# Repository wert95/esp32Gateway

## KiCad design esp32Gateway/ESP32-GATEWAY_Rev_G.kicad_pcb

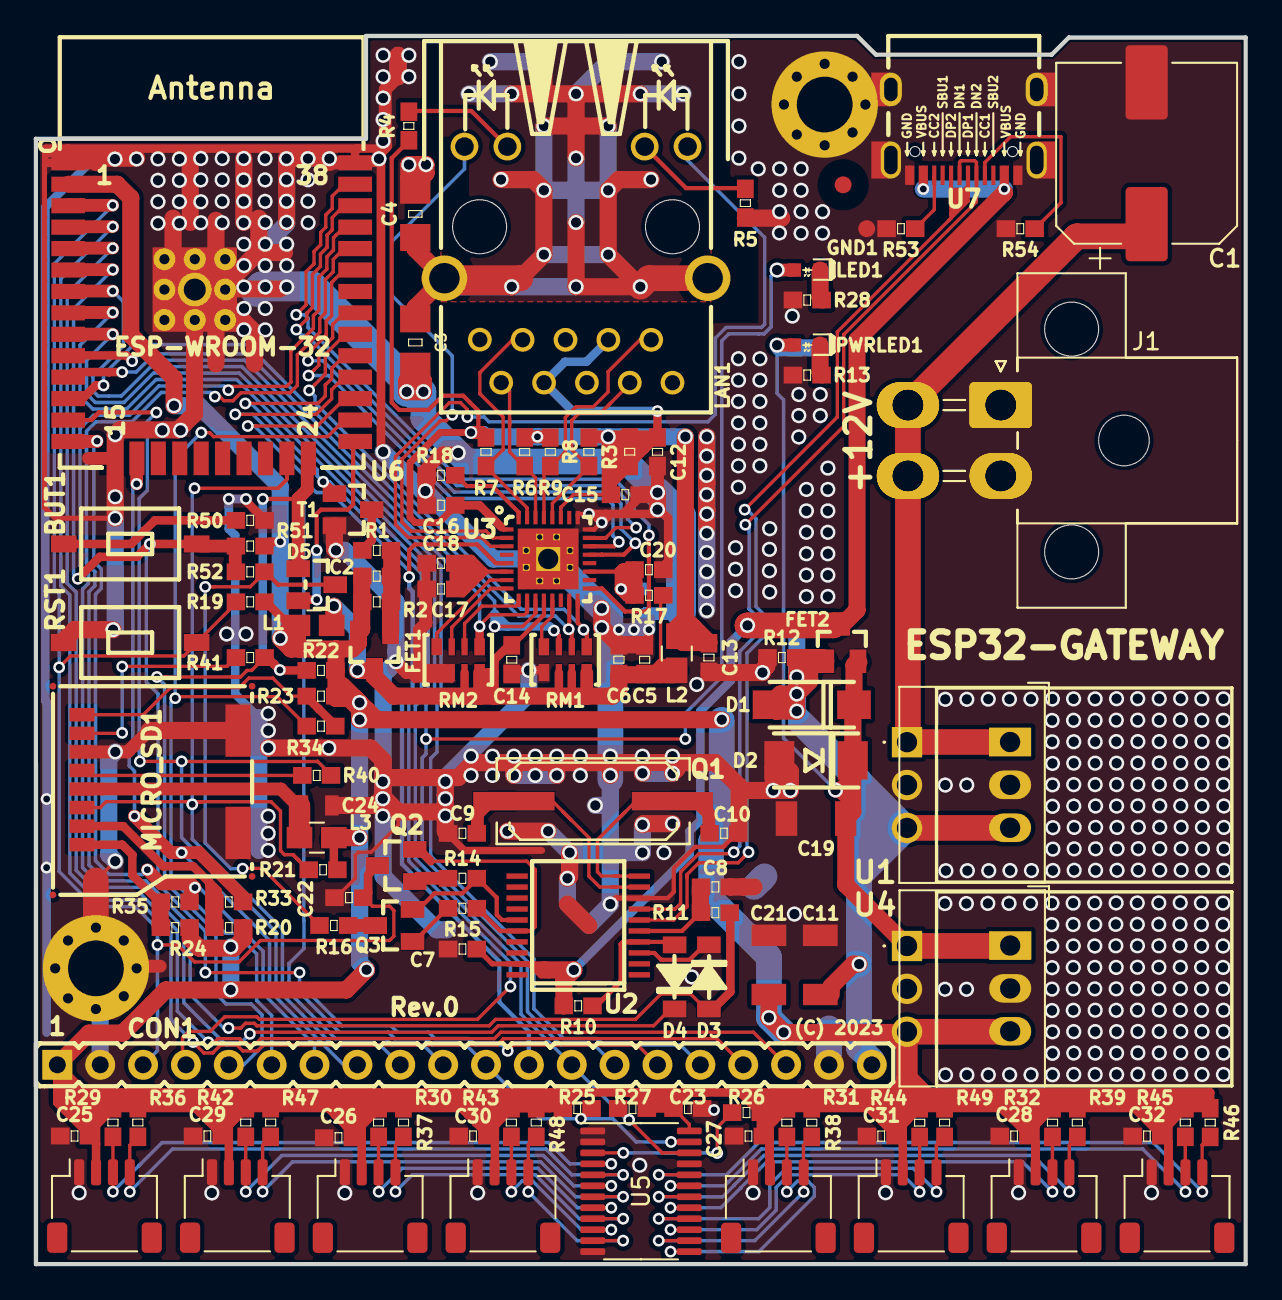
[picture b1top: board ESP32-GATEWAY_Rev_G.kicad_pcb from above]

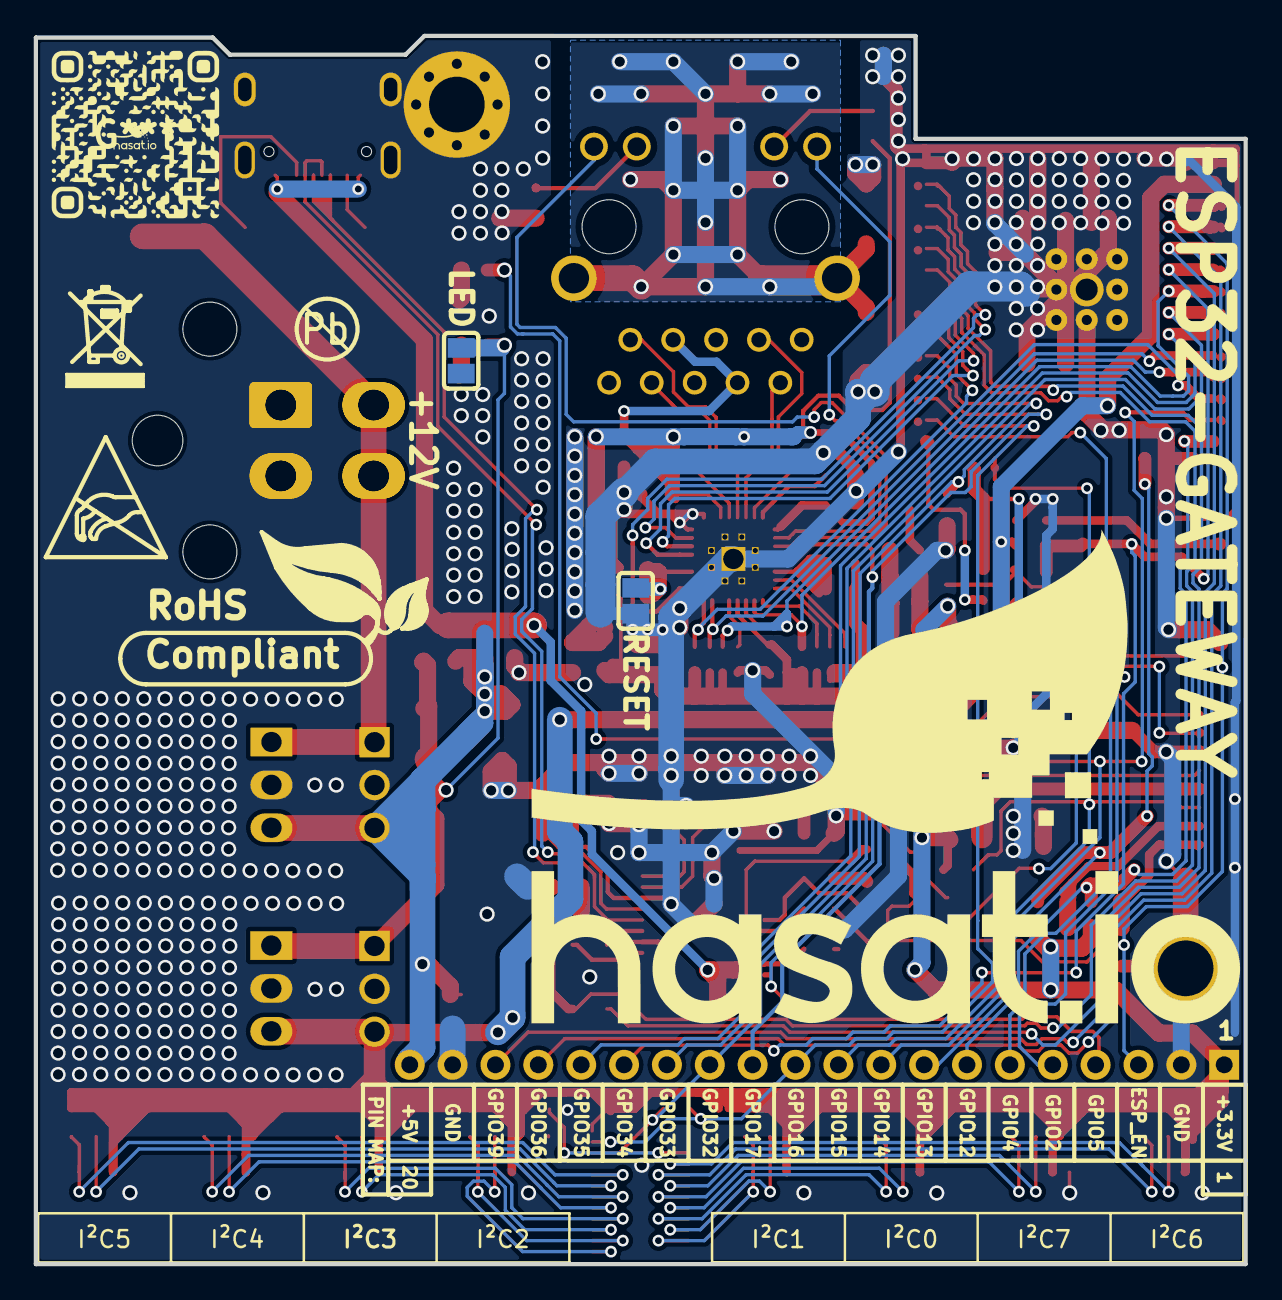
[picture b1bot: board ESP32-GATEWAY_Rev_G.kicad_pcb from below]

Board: 2 copper layers, 71.7 x 72.8 mm, 135 parts (6 on the bottom side), 94 nets.

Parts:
BUT1: T1107A(6x3,8x2,5MM)
C1: 220uF/50V/10*10mm; CP_Elec_10x10.5
C2, C5, C6, C7, C13: 22uF/6.3V/20%/X5R/C0603; 0603
C3: 1nF/2000V/10%/X7R/C1206; 1206
C4: NA(1nF/2000V/10%/X7R/C1206); 1206
C8, C12, C14, C15, C16, C18: 100nF/50V/20%/Y5V/C0603; 0603
C9, C10: 27pF/50V/5%/C0G/C0603; 0603
C11, C19, C21: 330uF/6.3V/20%/X5R/C1210; 1210
C17: 2.2uF/6.3V/10%/X5R/C0603; 0603
C20: NA(10uF/6.3V/20%/X5R/C0603); 0603
C22: 1uF/C0603; 0603
C23: 100nF/6.3V/20%/X5R/C0603; 0603
C24: 47uF/6.3V/20%/X5R/C0805; 0805
C25, C26, C27, C28, C29, C30, C31, C32: 1uF/6.3V/20%/X5R/C0603; 0603
CON1: NA(NH1x20); HN1x20
D1: 1N5822/SS34/SMA; SMA-KA
D2: SMBJ6.0A(DO-214AA); DO214AA_1(K)-2(A)
D3, D4: 1N5819S4/SOD123; SOD-123_1C-2A_KA
D5: BAT54C(SOT23-3); SOT23-3
FET1, FET2: WPM2015-3/TR; SOT23
FID3: Fiducial; Fiducial1x3
GND1: TESTPAD; TESTPAD_40-ROUND
I²C0, I²C1, I²C2, I²C3, I²C4, I²C5, I²C6, I²C7: Conn_01x04_P1.00mm_Stemma qt/Qwiic; JST_SH_SM04B-SRSS-TB_1x04-1MP_P1.00mm_Horizontal
J1: Conn_02x02_P4.20mm_Molex_Horizontal; Molex_Mini-Fit_Jr_5569-04A1_2x02_P4.20mm_Horizontal
L1: NA(FB0805/600R/2A); L_0805_5MIL_DWS
L2, L3: FB0805/600R/2A; L_0805_5MIL_DWS
LAN1: RJLD-060TC1(LPJ4013EDNL); RJLBC-060TC1
LED: Closed; SJ
LED1: LED/GREEN/0603; LED_0603_KA
MH1, MH2: Mounting_hole_Shield_3.3mm
MICRO_SD1: TFC-WXCP11-08-LF
PWRLED1: LED/RED/0603; LED_0603_KA
Q1: Q12MHz/20pF/30ppm/2P/HC-49SM(SMD); Q_49U3HMS
Q2, Q3: BC817-40(SOT23); SOT23
R1, R14, R15: 1k/R0603; 0603
R2, R10, R11, R17, R19, R21, R26, R51: 10k/R0603; 0603
R3: 0R(Board_Mounted); 0603
R4, R5: 330R/R0603; 0603
R6, R7, R8, R9: 49.9R/1%/R0603; 0603
R12: 1M/R0603; 0603
R13, R20, R22, R23, R24, R28: 2.2k/R0603; 0603
R16, R41, R50: 220R/R0603; 0603
R18: 12.1k/1%/R0603; 0603
R25, R27, R29, R30, R31, R32, R36, R37, R38, R39, R42, R43, R44, R45, R46, R47, R48, R49: 4.7k/R0603; 0603
R33, R34, R35, R52: NA/R0603; 0603
R40: 10R/R0603; 0603
R53, R54: 5.1k/R0603; 0603
RESET: Opened; SJ
RM1, RM2: RA1206_(4X0603)_4B8_2.2k; R_MATRIX_4
RST1: T1107A(6x3,8x2,5MM)
Sign-Antistatic: Val**; LOGO_ANTISTATIC_1
Sign-RecyclBin: LOGO_RECYCLEBIN_1
Sign_Pb-Free: LOGO_PBFREE
Sign_RoHS: Val**; LOGO_ROHS_1
T1: DTC114YKA; SOT23
U1: K7805-2000R3L; K78122000R3L
U2: CH340T(SSOP20W); SSOP-20W
U3: LAN8710A-EZC(QFN32); QFN32_EP(33)_5.00x5.00x0.90mm_Pitch_0.50mm
U4: K7803-2000R3L; K78122000R3L
U5: TCA9548APWR; TSSOP-24_4.4x7.8mm_P0.65mm
U6: ESP32-WROOM-32D-4MB; ESP-WROOM-32_MODULE
U7: USB-C-16P-F(A40-00119-A52-12); USB2.0_TYPE-C(A40-00119-A52-12)

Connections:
+3.3VLAN: C5.1, C6.1, C14.1, FET1.3, L1.2, L2.1, R17.2, RM1.1.2, RM1.2.2, RM1.3.2, RM2.3.1, RM2.4.1, U3.12 (VDDIO)
+3V3: C2.1, C21.1, C23.2, C25.2, C26.2, C27.2, C28.2, C29.2, C30.2, C31.2, C32.2, CON1.1, FET1.2, I²C0.2, I²C1.2, I²C2.2, I²C3.2, I²C4.2, I²C5.2, I²C6.2, I²C7.2, L1.1, L3.1, R2.1, R19.1, R20.1, R21.1, R22.1, R23.1, R24.1, R25.1, R26.1, R27.1, R29.1, R30.1, R31.1, R32.1, R36.1, R37.1, R38.1, R39.1, R42.1, R43.1, R44.1, R45.1, R46.1, R47.1, R48.1, R49.1, R51.1, U4.3 (OUT), U5.24 (VCC), U6.2 (3V3)
+5V: C19.1, D1.1 (K), D2.1 (K), FET2.2, LED.2, PWRLED1.2 (A), U4.1 (IN)
+5V_EXT: C11.1, CON1.20, D1.2 (A), FET2.1, R12.1, U1.3 (OUT)
/+5V_USB: C7.1, FET2.3, R10.1, U2.19 (VCC), U7.A4 (VBUS), U7.A9 (VBUS), U7.B4 (VBUS), U7.B9 (VBUS)
/D_Com: D5.3 (CC), R16.2, R52.2
/ESP_EN: C22.1, CON1.3, Q2.3 (C), R19.2, RST1.1, U6.3 (EN)
/GPI34\BUT1: BUT1.1, CON1.15, R51.2, R52.1, U6.6 (GPI34/ADC1_CH6/RTC_GPIO4)
/GPI35: CON1.16, U6.7 (GPI35/ADC1_CH7/RTC_GPIO5)
/GPI36: CON1.17, U6.4 (GPI36/SENSOR_VP/ADC_H/ADC1_CH0/RTC_GPIO0)
/GPI39: CON1.18, U6.5 (GPI39/SENSOR_VN/ADC1_CH3/ADC_H/RTC_GPIO3)
/GPIO0: D5.2 (A2), U6.25 (GPIO0/ADC2_CH1/TOUCH1/RTC_GPIO11/CLK_OU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)
/GPIO1\U0TXD: D4.1 (K), U6.35 (GPIO1/U0TXD/CLK_OUT3/EMAC_RXD2)
/GPIO2\HS2_DATA0: CON1.5, D5.1 (A1), R22.2, R41.1, U6.24 (GPIO2/ADC2_CH2/TOUCH2/RTC_GPIO12/HSPIWP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)
/GPIO3\U0RXD: D3.2 (A), R11.2, U6.34 (GPIO3/U0RXD/CLK_OUT2)
/GPIO4\HS2_DATA1: CON1.6, R34.1, U6.26 (GPIO4/ADC2_CH0/TOUCH0/RTC_GPIO10/HSPIHD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)
/GPIO5\PHY_PWR: CON1.4, T1.1 (B), U6.29 (GPIO5/VSPICS0/HS1_DATA6/EMAC_RX_CLK)
/GPIO12\HS2_DATA2: CON1.7, R35.1, U6.14 (GPIO12/ADC2_CH5/TOUCH5/RTC_GPIO15/MTDI/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)
/GPIO13\HS2_DATA3: CON1.8, R33.1, U6.16 (GPIO13/ADC2_CH4/TOUCH4/RTC_GPIO14/MTCK/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)
/GPIO14\HS2_CLK: CON1.9, R40.1, U6.13 (GPIO14/ADC2_CH6/TOUCH6/RTC_GPIO16/MTMS/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)
/GPIO15\HS2_CMD: CON1.10, MICRO_SD1.3 (CMD/DI), R21.2, U6.23 (GPIO15/ADC2_CH3/TOUCH3/MTDO/HSPICS0/RTC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)
/GPIO16: CON1.11, R25.2, U5.23 (SDA), U6.27 (GPIO16/HS1_DATA4/U2RXD/EMAC_CLK_OUT)
/GPIO17\EMAC_CLK_OUT_180: CON1.12, U3.5 (XTAL1/CLKIN), U6.28 (GPIO17/HS1_DATA5/U2TXD/EMAC_CLK_OUT_180)
/GPIO18\MDIO(RMII): RM1.1.1, U3.16 (MDIO), U6.30 (GPIO18/VSPICLK/HS1_DATA7)
/GPIO19\EMAC_TXD0(RMII): U3.22 (TXD0), U6.31 (GPIO19/VSPIQ/U0CTS/EMAC_TXD0)
/GPIO21\EMAC_TX_EN(RMII): U3.21 (TXEN), U6.33 (GPIO21/VSPIHD/EMAC_TX_EN)
/GPIO22\EMAC_TXD1(RMII): U3.23 (TXD1), U6.36 (GPIO22/VSPIWP/U0RTS/EMAC_TXD1)
/GPIO23\MDC(RMII): U3.17 (MDC), U6.37 (GPIO23/VSPID/HS1_STROBE)
/GPIO25\EMAC_RXD0(RMII): RM1.3.1, U3.11 (RXD0/MODE0), U6.10 (GPIO25/DAC_1/ADC2_CH8/RTC_GPIO6/EMAC_RX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)
/GPIO26\EMAC_RXD1(RMII): RM2.4.2, U3.10 (RXD1/MODE1), U6.11 (GPIO26/DAC_2/ADC2_CH9/RTC_GPIO7/EMAC_RX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)
/GPIO27\EMAC_RX_CRS_DV: RM1.2.1, U3.15 (COL/CRS_DV/MODE2), U6.12 (GPIO27/ADC2_CH7/TOUCH7/RTC_GPIO17/EMAC_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)
/GPIO32: CON1.13, R27.2, U5.22 (SCL), U6.8 (GPIO32/XTAL_32K_P/ADC1_CH4/TOUCH9/RTC_G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)
/GPIO33\LED: CON1.14, LED1.2 (A), U6.9 (GPIO33/XTAL_32K_N/ADC1_CH5/TOUCH8/RTC_G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)
/PHYAD0: RM1.4.1, U3.13 (RXER/RXD4/PHYAD0)
/PHYAD1: RM2.1.2, U3.7 (RXCLK/PHYAD1)
/PHYAD2: RM2.2.2, U3.8 (RXD3/PHYAD2)
/RMIISEL: RM2.3.2, U3.9 (RXD2/RMIISEL)
/VDD1A-2A: C12.1, C13.1, C15.1, C16.1, L2.2, LAN1.3 (COM), LAN1.6 (NC), R3.1, R3.2, R4.1, R6.1, R7.1, R8.1, R9.1, U3.1 (VDD2A), U3.27 (VDD1A)
/VDDCR: C17.1, C18.1, U3.6 (VDDCR)
GND: C1.2, C3.2, C4.2, C5.2, C6.2, C7.2, C8.2, C9.2, C10.2, C11.2, C12.2, C13.2, C14.2, C15.2, C16.2, C17.2, C18.2, C19.2, C20.1, C21.2, C22.2, C23.1, C24.2, C25.1, C26.1, C27.1, C28.1, C29.1, C30.1, C31.1, C32.1, CON1.2, CON1.19, D2.2 (A), GND1.1 (Pad), I²C0.1, I²C1.1, I²C2.1, I²C3.1, I²C4.1, I²C5.1, I²C6.1, I²C7.1, J1.1, J1.2, MH1.GND1, MH2.GND1, MICRO_SD1.6 (VSS), MICRO_SD1.SH1 (PACK1), MICRO_SD1.SH2 (PACK2), R5.2, R12.2, R13.2, R18.2, R28.1, R50.2, R53.1, R54.1, RESET.1, RM1.4.2, RM2.1.1, RM2.2.1, RST1.2, T1.2 (E), U1.2 (GND), U2.8 (GND), U3.24 (TXD2), U3.25 (TXD3), U3.33 (GND), U4.2 (GND), U5.1 (A0), U5.2 (A1), U5.12 (GND), U5.21 (A2), U6.1 (GND), U6.15 (GND), U6.38 (GND), U6.39 (THERMAL_PAD), U7.0 (SHELL), U7.A1 (GND), U7.A12 (GND), U7.B1 (GND), U7.B12 (GND)
unnamed: BUT1.2, R50.1
unnamed: C1.1, J1.3, J1.4, U1.1 (IN)
unnamed: C2.2, FET1.1, R1.1, R2.2
unnamed: C3.1, C4.1, LAN1.GND1, LAN1.GND2
unnamed: C8.1, R11.1, U2.5 (V3)
unnamed: C9.1, Q1.1, U2.9 (XI)
unnamed: C10.1, Q1.2, U2.10 (XO)
unnamed: C20.2, R17.1, RESET.2, U3.19 (NRST)
unnamed: C24.1, L3.2, MICRO_SD1.4 (VDD)
unnamed: D3.1 (K), U2.3 (TXD)
unnamed: D4.2 (A), R10.2, U2.4 (RXD)
unnamed: I²C6.3, R29.2, U5.4 (SD0)
unnamed: I²C6.4, R36.2, U5.5 (SC0)
unnamed: I²C7.3, R42.2, U5.6 (SD1)
unnamed: I²C7.4, R47.2, U5.7 (SC1)
unnamed: I²C0.3, R30.2, U5.8 (SD2)
unnamed: I²C0.4, R37.2, U5.9 (SC2)
unnamed: I²C1.3, R43.2, U5.10 (SD3)
unnamed: I²C1.4, R48.2, U5.11 (SC3)
unnamed: I²C2.3, R31.2, U5.13 (SD4)
unnamed: I²C2.4, R38.2, U5.14 (SC4)
unnamed: I²C3.3, R44.2, U5.15 (SD5)
unnamed: I²C3.4, R49.2, U5.16 (SC5)
unnamed: I²C4.3, R32.2, U5.17 (SD6)
unnamed: I²C4.4, R39.2, U5.18 (SC6)
unnamed: I²C5.3, R45.2, U5.19 (SD7)
unnamed: I²C5.4, R46.2, U5.20 (SC7)
unnamed: LAN1.1 (TD+), R9.2, U3.29 (TXP)
unnamed: LAN1.2 (TD-), R8.2, U3.28 (TXN)
unnamed: LAN1.7 (RD+), R7.2, U3.31 (RXP)
unnamed: LAN1.8 (RD-), R6.2, U3.30 (RXN)
unnamed: LAN1.AG1 (AG), R4.2
unnamed: LAN1.AY1 (AY), U3.3 (LED1/REGOFF)
unnamed: LAN1.KG1 (KG), U3.2 (LED2/NINTSEL)
unnamed: LAN1.KY1 (KY), R5.1
unnamed: LED1.1 (K), R28.2
unnamed: MICRO_SD1.1 (DAT2/RES), R24.2, R35.2
unnamed: MICRO_SD1.2 (CD/DAT3/CS), R20.2, R33.2
unnamed: MICRO_SD1.5 (CLK/SCLK), R40.2
unnamed: MICRO_SD1.7 (DAT0/DO), R41.2
unnamed: MICRO_SD1.8 (DAT1/RES), R23.2, R34.2
unnamed: PWRLED1.1 (K), R13.1
unnamed: Q2.1 (B), R14.2
unnamed: Q2.2 (E), R15.1, U2.16 (RTS#)
unnamed: Q3.1 (B), R15.2
unnamed: Q3.2 (E), R14.1, U2.15 (DTR#)
unnamed: Q3.3 (C), R16.1
unnamed: R1.2, T1.3 (C)
unnamed: R18.1, U3.32 (RBIAS)
unnamed: R26.2, U5.3 (~RESET)
unnamed: R53.2, U7.B5 (CC2)
unnamed: R54.2, U7.A5 (CC1)
unnamed: U2.6 (UD+), U7.A6 (DP1), U7.B6 (DP2)
unnamed: U2.7 (UD-), U7.A7 (DN1), U7.B7 (DN2)

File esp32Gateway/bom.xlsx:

Id | Tasarımcı | Paket | Miktar | Tasarım | Supplier and ref | Column1
1 | BUT1,RST1 | T1107A(6x3,8x2,5MM) | 2 | T1107A(6x3,8x2,5MM)
2 | C1 | CP_Elec_10x10.5 | 1 | 220uF/50V/10*10mm
3 | C12,C14,C15,C16,C18,C8 | 0603 | 6 | 100nF/50V/20%/Y5V/C0603
4 | C17 | 0603 | 1 | 2.2uF/6.3V/10%/X5R/C0603
5 | C19,C11,C21 | 1210 | 3 | 330uF/6.3V/20%/X5R/C1210
6 | C20 | 0603 | 1 | NA(10uF/6.3V/20%/X5R/C0603)
7 | C22 | 0603 | 1 | 1uF/C0603
8 | C23 | 0603 | 1 | 100nF/6.3V/20%/X5R/C0603
9 | C24 | 0805 | 1 | 47uF/6.3V/20%/X5R/C0805
10 | C26,C32,C25,C28,C31,C29,C30,C27 | 0603 | 8 | 1uF/6.3V/20%/X5R/C0603
11 | C3 | 1206 | 1 | 1nF/2000V/10%/X7R/C1206
12 | C4 | 1206 | 1 | NA(1nF/2000V/10%/X7R/C1206)
13 | C5,C6,C13,C7,C2 | 0603 | 5 | 22uF/6.3V/20%/X5R/C0603
14 | C9,C10 | 0603 | 2 | 27pF/50V/5%/C0G/C0603
15 | CON1 | HN1x20 | 1 | NA(NH1x20)
16 | D1 | SMA-KA | 1 | 1N5822/SS34/SMA
17 | D2 | DO214AA_1(K)-2(A) | 1 | SMBJ6.0A(DO-214AA)
18 | D4,D3 | SOD-123_1C-2A_KA | 2 | 1N5819S4/SOD123
19 | D5 | SOT23-3 | 1 | BAT54C(SOT23-3)
20 | FET2,FET1 | SOT23 | 2 | WPM2015-3/TR
21 | GND1 | TESTPAD_40-ROUND | 1 | TESTPAD
22 | I²C1,I²C0,I²C5,I²C6,I²C3,I²C4,I²C7,I²C2 | JST_SH_SM04B-SRSS-TB_1x04-1MP_P1.00mm_Horizontal | 8 | Conn_01x04_P1.00mm_Stemma qt/Qwiic
23 | J1 | Molex_Mini-Fit_Jr_5569-04A1_2x02_P4.20mm_Horizontal | 1 | Conn_02x02_P4.20mm_Molex_Horizontal
24 | L1 | L_0805_5MIL_DWS | 1 | NA(FB0805/600R/2A)
25 | L2,L3 | L_0805_5MIL_DWS | 2 | FB0805/600R/2A
26 | LAN1 | RJLBC-060TC1 | 1 | RJLD-060TC1(LPJ4013EDNL)
27 | LED_E1 | SJ | 1 | Closed
28 | LED1 | LED_0603_KA | 1 | LED/GREEN/0603
29 | MICRO_SD1 | TFC-WXCP11-08-LF | 1 | TFC-WXCP11-08-LF
30 | PHY_RST1 | SJ | 1 | Opened
31 | PWRLED1 | LED_0603_KA | 1 | LED/RED/0603
32 | Q1 | Q_49U3HMS | 1 | Q12MHz/20pF/30ppm/2P/HC-49SM(SMD)
33 | Q2,Q3 | SOT23 | 2 | BC817-40(SOT23)
34 | R10,R17,R11,R51,R2,R21,R19,R26 | 0603 | 8 | 10k/R0603
35 | R12 | 0603 | 1 | 1M/R0603
36 | R13,R28,R20,R22,R23,R24 | 0603 | 6 | 2.2k/R0603
37 | R14,R15,R1 | 0603 | 3 | 1k/R0603
38 | R18 | 0603 | 1 | 12.1k/1%/R0603
39 | R3 | 0603 | 1 | 0R(Board_Mounted)
40 | R4,R5 | 0603 | 2 | 330R/R0603
41 | R40 | 0603 | 1 | 10R/R0603
42 | R43,R29,R37,R49,R44,R32,R36,R27,R48,R45,R47,R38,R30,R46,R42,R25,R39,R31 | 0603 | 18 | 4.7k/R0603
43 | R50,R16,R41 | 0603 | 3 | 220R/R0603
44 | R52,R35,R34,R33 | 0603 | 4 | NA/R0603
45 | R53,R54 | 0603 | 2 | 5.1k/R0603
46 | R6,R7,R8,R9 | 0603 | 4 | 49.9R/1%/R0603
47 | REF** | Molex_Mini-Fit_Jr_5569-04A2_2x02_P4.20mm_Horizontal | 1 | Molex_Mini-Fit_Jr_5569-04A2_2x02_P4.20mm_Horizontal
48 | RM2,RM1 | R_MATRIX_4 | 2 | RA1206_(4X0603)_4B8_2.2k
49 | T1 | SOT23 | 1 | DTC114YKA
50 | U1 | K78122000R3L | 1 | K7805-2000R3L
51 | U2 | SSOP-20W | 1 | CH340T(SSOP20W)
52 | U3 | QFN32_EP(33)_5.00x5.00x0.90mm_Pitch_0.50mm | 1 | LAN8710A-EZC(QFN32)
53 | U4 | K78122000R3L | 1 | K7803-2000R3L
54 | U5 | TSSOP-24_4.4x7.8mm_P0.65mm | 1 | TCA9548APWR
55 | U6 | ESP-WROOM-32_MODULE | 1 | ESP32-WROOM-32D-4MB
56 | U7 | USB2.0_TYPE-C(A40-00119-A52-12) | 1 | USB-C-16P-F(A40-00119-A52-12)

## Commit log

2023-02-19 rev0

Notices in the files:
esp32Gateway/ESP32-GATEWAY_Rev_G.kicad_pcb:
(C) 2023
